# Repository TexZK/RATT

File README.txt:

RATT - Relatively Accurate TurnTable

For information about the project, please refer to:
./doc/reports/Report.pdf

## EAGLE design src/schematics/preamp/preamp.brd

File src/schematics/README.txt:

Source code for PCB schematics, developed with CadSoft EAGLE 6.2.0.

http://www.cadsoftusa.com/eagle/

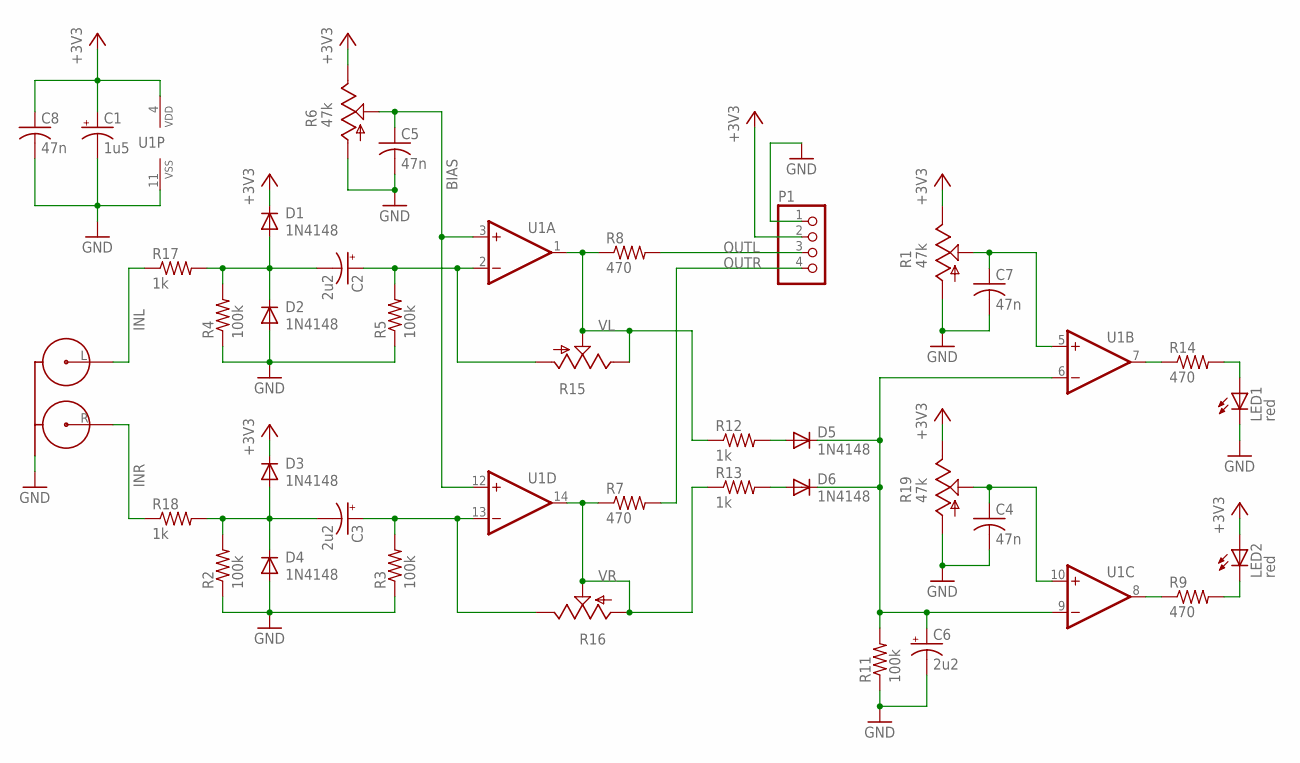
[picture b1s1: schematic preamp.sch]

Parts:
C1: 1u5; E2-4
C2, C3: 2u2; E2,5-5
C4, C5, C7, C8: 47n; C050-025X075
C6: 2u2; E2,5-6
D1, D2, D3, D4, D5, D6: 1N4148; DO35-5
LED1, LED2: red; LED3MM
P1: PINHD-1X4; 1X04
R1, R6, R19: 47k; PT-10S
R2, R3, R4, R5, R11: 100k; 0204/5
R7, R8, R9, R14: 470; 0204/5
R12, R13, R17, R18: 1k; 0204/5
R15, R16: TRIM_US-S63S; S63S
RCA1: RCA-2V
U1: MCP6024-I/P; DIL14

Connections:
+3V3: C1.+, C8.1, D1.C, D3.C, LED2.A, P1.2, R1.E, R6.E, R19.E, U1.4 (VDD)
BIAS: C5.1, R6.S, U1.3 (+IN), U1.12 (+IN)
GND: C1.-, C4.2, C5.2, C6.-, C7.2, C8.2, D2.A, D4.A, LED1.K (C), P1.1, R1.A, R2.1, R3.1, R4.1, R5.1, R6.A, R11.1, R19.A, RCA1.SHIELD, U1.11 (VSS)
INL: R17.1, RCA1.L
INR: R18.1, RCA1.R
unnamed: C4.1, R19.S, U1.10 (+IN)
unnamed: R9.1, U1.8 (OUT)
unnamed: C3.-, D3.A, D4.C, R2.2, R18.2
unnamed: C6.+, D5.C, D6.C, R11.2, U1.6 (-IN), U1.9 (-IN)
unnamed: C2.+, R5.2, R15.A, U1.2 (-IN)
unnamed: C7.1, R1.S, U1.5 (+IN)
unnamed: LED1.A, R14.2
unnamed: C2.-, D1.A, D2.C, R4.2, R17.2
unnamed: C3.+, R3.2, R16.E, U1.13 (-IN)
unnamed: D5.A, R12.2
unnamed: D6.A, R13.2
unnamed: LED2.K (C), R9.2
unnamed: R14.1, U1.7 (OUT)
OUTL: P1.3, R8.2
OUTR: P1.4, R7.2
VL: R8.1, R12.1, R15.E, R15.S, U1.1 (OUT)
VR: R7.1, R13.1, R16.A, R16.S, U1.14 (OUT)

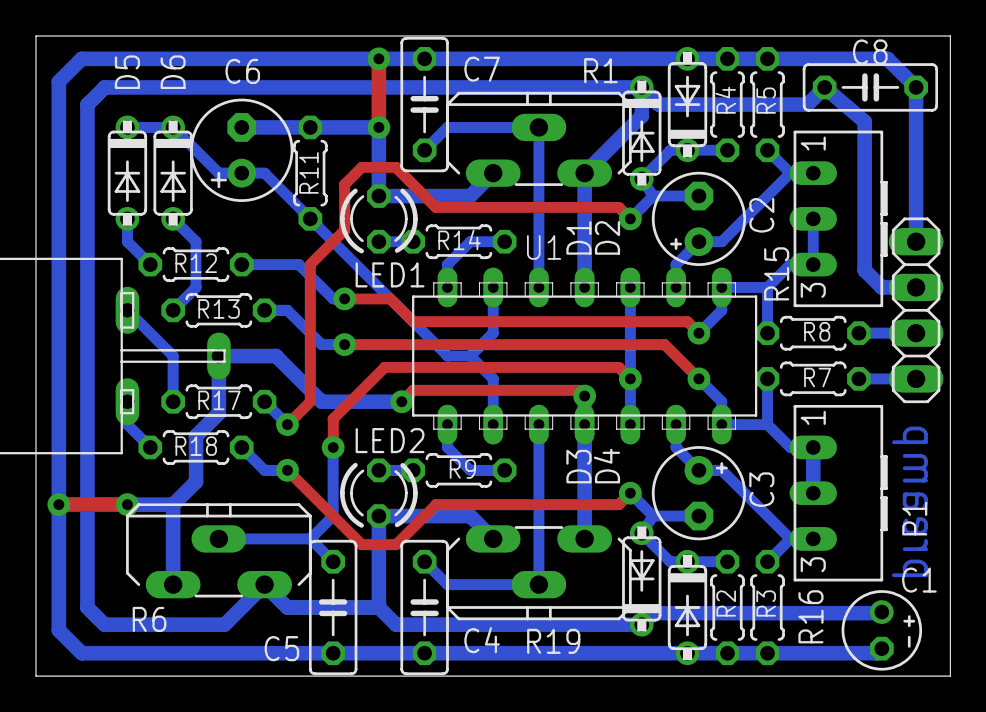
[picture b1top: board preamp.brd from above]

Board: 2 copper layers, 50.8 x 35.6 mm, 37 parts (0 on the bottom side), 22 nets.

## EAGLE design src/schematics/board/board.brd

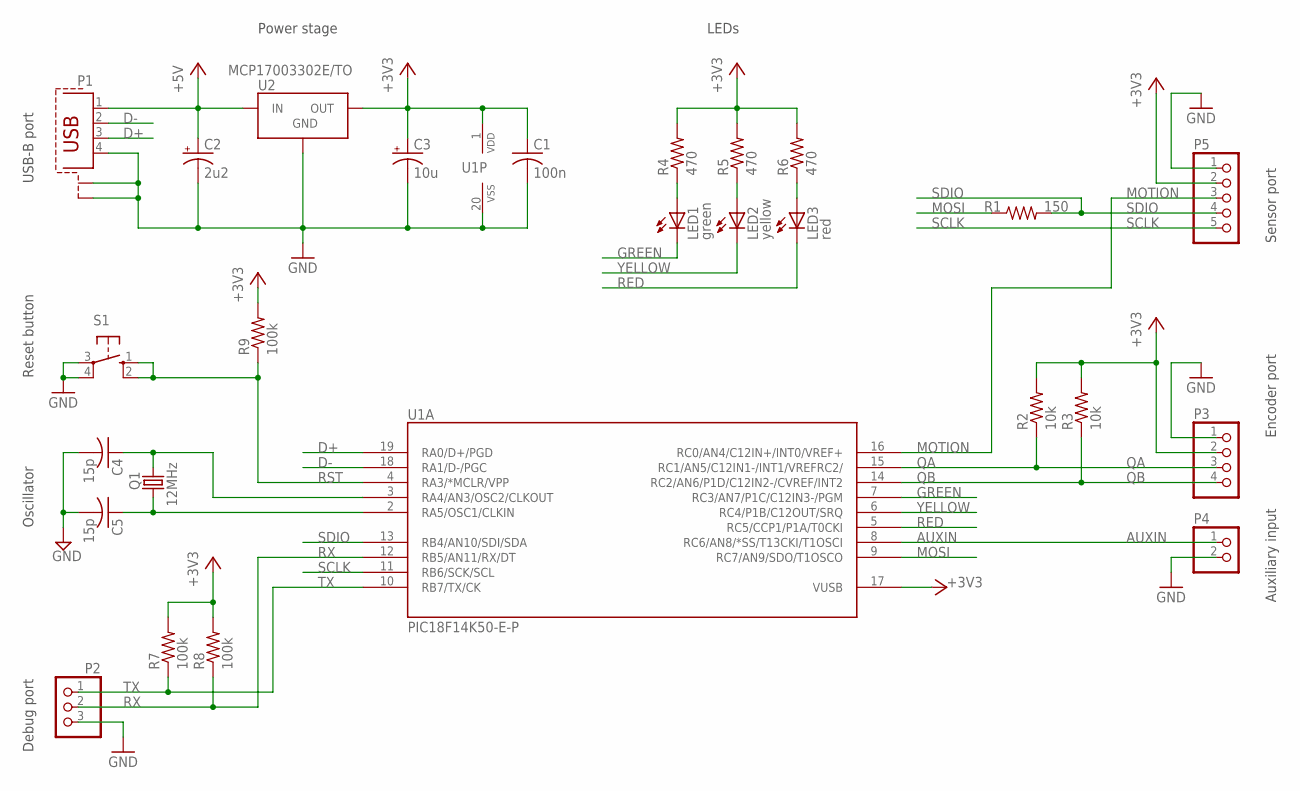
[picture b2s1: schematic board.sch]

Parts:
C1: 100n; C025-025X050
C2: 2u2; E2-5
C3: 10u; E2-5
C4, C5: 15p; C025-025X050
LED1: green; LED3MM
LED2: yellow; LED3MM
LED3: red; LED3MM
P1: PN61729-S
P2: PINHD-1X3; 1X03
P3: PINHD-1X4; 1X04
P4: PINHD-1X2; 1X02
P5: PINHD-1X5; 1X05
Q1: 12MHz; HC49/S
R1: 150; 0207/10
R2, R3: 10k; 0204/5
R4, R5, R6: 470; 0204/5
R7, R8, R9: 100k; 0204/5
S1: 10-XX; B3F-10XX
U1: PIC18F14K50-E-P; DIL20
U2: MCP17003302E/TO; TO-92

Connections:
+3V3: C1.1, C3.+, P3.2, P5.2, R2.2, R3.2, R4.2, R5.2, R6.2, R7.2, R8.2, R9.2, U1.1 (VDD), U1.17 (VUSB), U2.OUT
+5V: C2.+, P1.1, U2.IN
AUXIN: P4.1, U1.8 (RC6/AN8/*SS/T13CKI/T1OSCI)
D+: P1.3, U1.19 (RA0/D+/PGD)
D-: P1.2, U1.18 (RA1/D-/PGC)
GND: C1.2, C2.-, C3.-, C4.2, C5.2, P1.4, P1.S1, P1.S2, P2.3, P3.1, P4.2, P5.1, S1.3, S1.4 (P1), U1.20 (VSS), U2.GND
GREEN: LED1.K (C), U1.7 (RC3/AN7/P1C/C12IN3-/PGM)
MOSI: R1.1, U1.9 (RC7/AN9/SDO/T1OSCO)
MOTION: P5.3, U1.16 (RC0/AN4/C12IN+/INT0/VREF+)
unnamed: LED3.A, R6.1
unnamed: C4.1, Q1.1, U1.3 (RA4/AN3/OSC2/CLKOUT)
unnamed: C5.1, Q1.2, U1.2 (RA5/OSC1/CLKIN)
unnamed: LED2.A, R5.1
unnamed: LED1.A, R4.1
QA: P3.3, R2.1, U1.15 (RC1/AN5/C12IN1-/INT1/VREFRC2/)
QB: P3.4, R3.1, U1.14 (RC2/AN6/P1D/C12IN2-/CVREF/INT2)
RED: LED3.K (C), U1.5 (RC5/CCP1/P1A/T0CKI)
RST: R9.1, S1.1 (S), S1.2 (S1), U1.4 (RA3/*MCLR/VPP)
RX: P2.2, R8.1, U1.12 (RB5/AN11/RX/DT)
SCLK: P5.5, U1.11 (RB6/SCK/SCL)
SDIO: P5.4, R1.2, U1.13 (RB4/AN10/SDI/SDA)
TX: P2.1, R7.1, U1.10 (RB7/TX/CK)
YELLOW: LED2.K (C), U1.6 (RC4/P1B/C12OUT/SRQ)

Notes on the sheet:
Reset button
Oscillator
Debug port
USB-B port
Encoder port
Auxiliary input
Sensor port
Power stage
LEDs

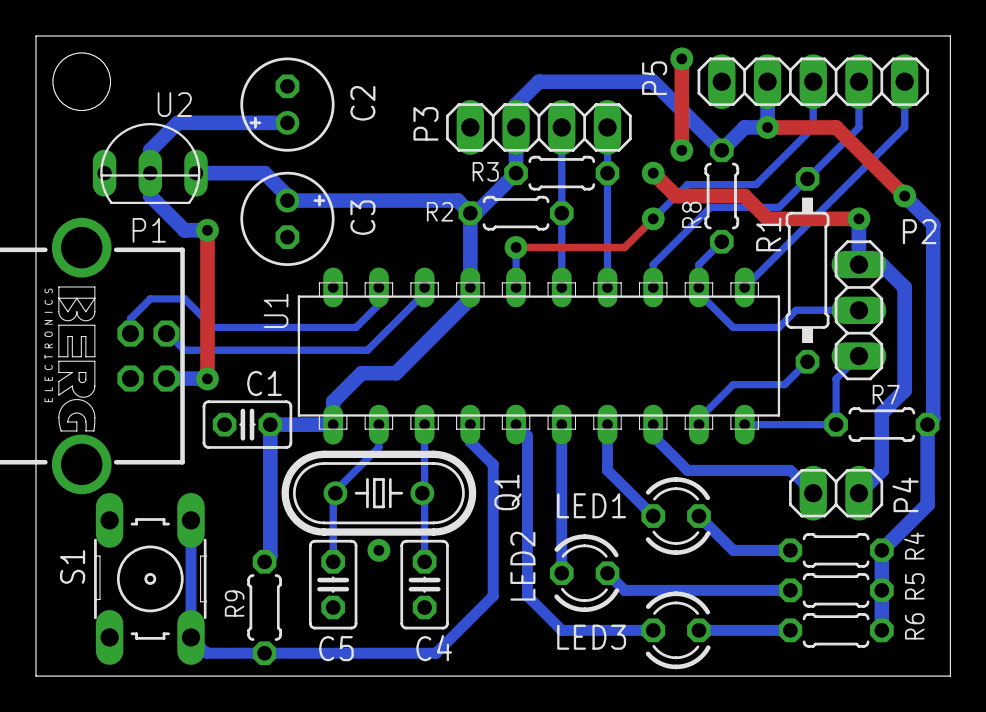
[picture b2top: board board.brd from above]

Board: 2 copper layers, 50.8 x 35.6 mm, 26 parts (0 on the bottom side), 23 nets.

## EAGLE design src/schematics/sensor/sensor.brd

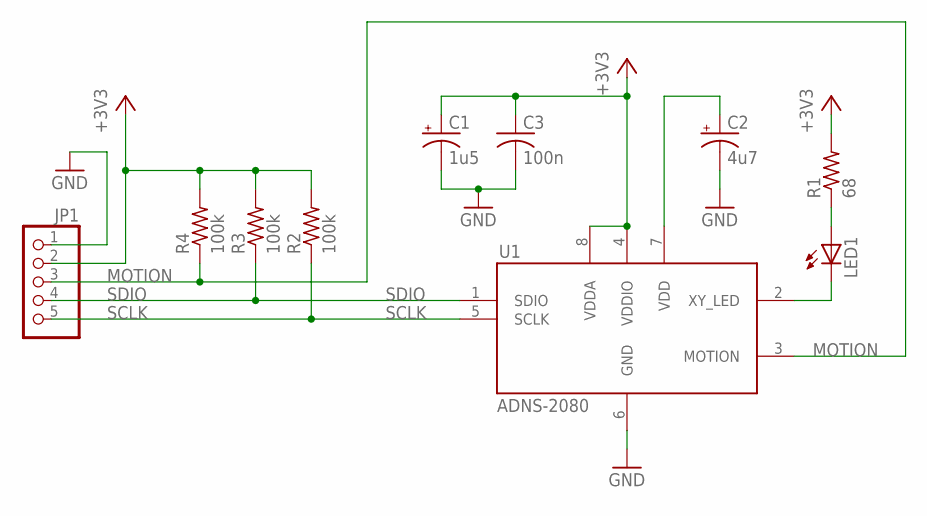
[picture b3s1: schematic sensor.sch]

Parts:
C1: 1u5; E2,5-5
C2: 4u7; E2,5-5
C3: 100n; C025-025X050
JP1: PINHD-1X5; 1X05
LED1: LED5MM
R1: 68; 0207/7
R2, R3, R4: 100k; 0204/5
U1: ADNS-2080; DIP8-OPTICAL

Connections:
+3V3: C1.+, C3.1, JP1.2, R1.2, R2.2, R3.2, R4.2, U1.4 (VDDIO), U1.8 (VDDA)
GND: C1.-, C2.-, C3.2, JP1.1, U1.6 (GND)
MOTION: JP1.3, R4.1, U1.3 (MOTION)
unnamed: C2.+, U1.7 (VDD)
unnamed: LED1.A, R1.1
unnamed: LED1.K (C), U1.2 (XY_LED)
SCLK: JP1.5, R2.1, U1.5 (SCLK)
SDIO: JP1.4, R3.1, U1.1 (SDIO)

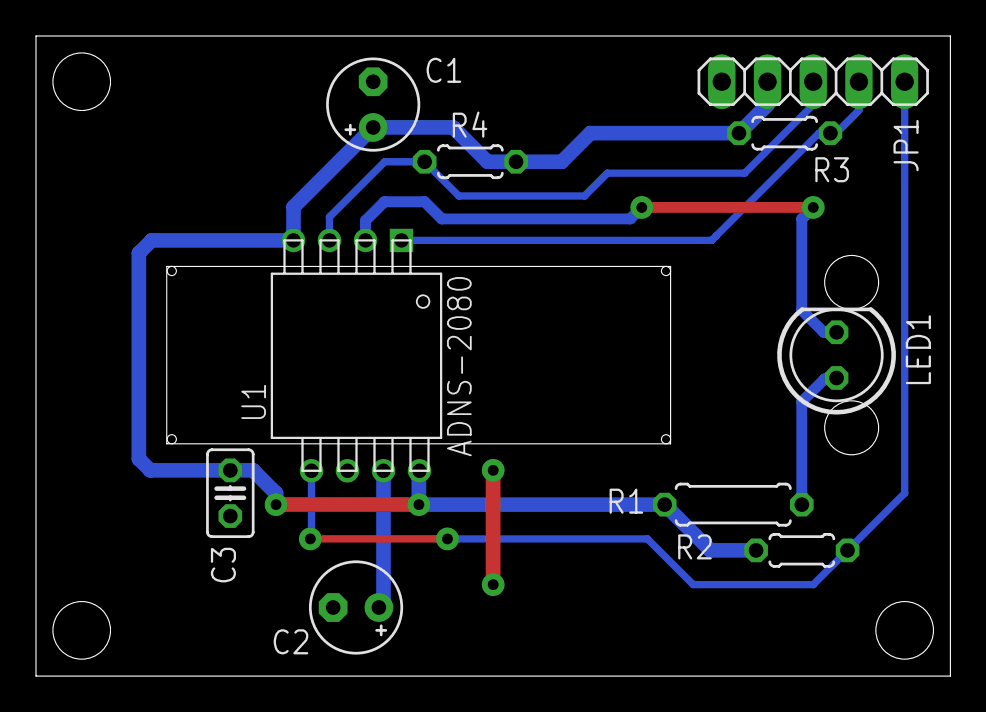
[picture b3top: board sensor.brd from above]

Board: 2 copper layers, 50.8 x 35.6 mm, 10 parts (0 on the bottom side), 8 nets.

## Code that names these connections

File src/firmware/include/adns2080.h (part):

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#define	ADNS_DLY_REST_DIS_MAX_S			      1				///< t_REST-DIS
#define	ADNS_DLY_PD_MAX_MS				     50				///< t_PD
#define	ADNS_DLY_WAKEUP_MAX_MS			     55				///< t_WAKEUP
#define	ADNS_DLY_R_SDIO_MAX_NS			    200				///< t_r-SDIO
#define	ADNS_DLY_F_SDIO_MAX_NS			    200				///< t_f-SDIO
#define	ADNS_DLY_DLY_SDIO_MAX_NS		    120				///< t_DLY-SDIO
#define	ADNS_DLY_HOLD_MIN_NS			    250				///< t_hold-SDIO
#define	ADNS_DLY_HOLD_MAX_NS			(1000000000 / ADNS_SPI_FREQ)	///< t_hold-SDIO
#define	ADNS_DLY_TIMEOUT_SDIO_MIN_MS	     50				///< t_timeout-SDIO
#define	ADNS_DLY_TSWR_MIN_MS			     20				///< t_SWR
#define	ADNS_DLY_TSWW_MIN_MS			     30				///< t_SWW
#define	ADNS_DLY_TSRX_MIN_NS			    250				///< t_SRW & t_SRR
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#define	ADNS_TRIS_MISO					TRISBbits.TRISB4	///< SPI MISO/SDI
#define	ADNS_TRIS_MOSI					TRISCbits.TRISC7	///< SPI MOSI/SDO
#define	ADNS_TRIS_SCLK					TRISBbits.TRISB6	///< SPI SCLK/SCK
#define	ADNS_TRIS_MOTION				TRISCbits.TRISC0	///< MOTION IRQ

#define	ADNS_PIN_MISO					PORTBbits.RB4		///< SPI MISO/SDI
#define	ADNS_PIN_MOSI					PORTCbits.RC7		///< SPI MOSI/SDO
#define	ADNS_PIN_SCLK					PORTBbits.RB6		///< SPI SCLK/SCK
#define	ADNS_PIN_MOTION					PORTCbits.RC0		///< MOTION IRQ

#define	ADNS_LAT_MISO					LATBbits.LATB4		///< SPI MISO/SDI
#define	ADNS_LAT_MOSI					LATCbits.LATC7		///< SPI MOSI/SDO
#define	ADNS_LAT_SCLK					LATBbits.LATB6		///< SPI SCLK/SCK
#define	ADNS_LAT_MOTION					LATCbits.LATC0		///< MOTION IRQ


// Interrupt settings
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// Register addresses (see datasheet for description)
#define	ADNS_REG_PROD_ID				0x00				///< Product ID
#define	ADNS_REG_REV_ID					0x01				///< Revision ID
#define	ADNS_REG_MOTION_ST				0x02				///< Motion Status 
#define	ADNS_REG_DELTA_X				0x03				///< Lower byte of Delta_X 
#define	ADNS_REG_DELTA_Y				0x04				///< Lower byte of Delta_Y
#define	ADNS_REG_SQUAL					0x05				///< Squal Quality
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#define	ADNS_REG_RESET					0x3A				///< Reset
#define	ADNS_REG_NOT_REV_ID				0x3F				///< Inverted Revision ID
#define	ADNS_REG_LED_CTRL				0x40				///< LED Control
#define	ADNS_REG_MOTION_CTRL			0x41				///< Motion Control
#define	ADNS_REG_BURST_READ_FIRST		0x42				///< Burst Read Starting Register 
#define	ADNS_REG_BURST_READ_LAST		0x44				///< Burst Read Ending Register
#define	ADNS_REG_REST_MODE_CONFIG		0x45				///< Rest Mode Coni  guration
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
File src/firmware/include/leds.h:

/**
 * LEDs driver.
 *
 * This file contains the definitions to handle the LEDs.
 *
 * @author Andrea "TexZK" Zoppi
 *
 */

#ifndef __LEDS_H__
#define	__LEDS_H__


//\\//\\//\\//\\//\\//\\//\\//\\//\\//\\//\\//\\//\\//\\//\\//\\//\\//\\//\\//
// HEADERS


//\\//\\//\\//\\//\\//\\//\\//\\//\\//\\//\\//\\//\\//\\//\\//\\//\\//\\//\\//
// GLOBAL DEFINITIONS

// Pins configuration
#define	LEDS_PORT				PORTC				///< LEDs port
#define	LEDS_TRIS				TRISC				///< LEDs port tristate
#define	LEDS_MASK				0b00111000			///< LEDs port/tristate mask

#define	LEDS_TRIS_GREEN			TRISCbits.TRISC3	///< Green LED pin tristate
#define	LEDS_TRIS_YELLOW		TRISCbits.TRISC4	///< Yellow LED pin tristate
#define	LEDS_TRIS_RED			TRISCbits.TRISC5	///< Red LED pin tristate

#define	LEDS_PIN_GREEN			PORTCbits.RC3		///< Green LED pin
#define	LEDS_PIN_YELLOW			PORTCbits.RC4		///< Yellow LED pin
#define	LEDS_PIN_RED			PORTCbits.RC5		///< Red LED pin

#define	LEDS_LAT_GREEN			LATCbits.LATC3		///< Green LED latch
#define	LEDS_LAT_YELLOW			LATCbits.LATC4		///< Yellow LED latch
#define	LEDS_LAT_RED			LATCbits.LATC5		///< Red LED latch


// Shorthands
#define	GREEN_LED				LEDS_LAT_GREEN		///< Shortcut for green LED bit
#define	YELLOW_LED				LEDS_LAT_YELLOW		///< Shortcut for yellow LED bit
#define	RED_LED					LEDS_LAT_RED		///< Shortcut for red LED bit

#define	LED_ON					0					///< Incoming current, LED lit
#define	LED_OFF					1					///< Pull-up, LED off


//\\//\\//\\//\\//\\//\\//\\//\\//\\//\\//\\//\\//\\//\\//\\//\\//\\//\\//\\//
// GLOBAL VARIABLES


//\\//\\//\\//\\//\\//\\//\\//\\//\\//\\//\\//\\//\\//\\//\\//\\//\\//\\//\\//
// GLOBAL PROTOTYPES

/**
 * Initializes the LEDs module.
 */
void Leds_Initialize( void );


/**
 * Turns LEDs as if they were bits:
 * 	GREEN	= bit 0,
 *	YELLOW	= bit 1,
 *	RED		= bit 2
 *
 * @param value
 *		3-bits value [RYG].
 */
#define	Leds_BinaryValue( value )	{	\
	GREEN_LED = !((value) & 0b001);		\
	YELLOW_LED = !((value) & 0b010);	\
	RED_LED = !((value) & 0b100);		\
}


#endif	/* !__LEDS_H__ */

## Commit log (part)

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2012-03-08 Datasheets and report source code
    Added datasheets for Avago ADNS-2080 and Microchip PIC18LF14K50, and the
    source code for the LaTeX report.
    Andrea Zoppi
2012-03-10 Sensor PCB updates
    Minor changes to the sensor module PCB layout.
    Andrea Zoppi
2012-03-10 PCBs updated
    Minor changes were done to both the main board and sensor module PCB
    layouts.
    Andrea Zoppi
2012-03-10 Code refactoring
    Main functions are now inside the "app" module.
    User USB functions were moved to the "usb_user" module.
    Andrea Zoppi
2012-03-11 Small fixes to firmware
    A bootloader definitions file was modularized, and a few initialization
    routines were rearranged (just some refactoring).
    Andrea Zoppi
2012-03-11 Added UART pull-ups
    Added pull-ups to the UART port, so that there are never mistaken signals.
    They are not critical, but may help in keeping consistent values,
    especially for the receiver.
    Andrea Zoppi
2012-03-12 Hand-written UART functions
    UART functions are now hand-written, because library functions provided by
    Microchip don't always work properly.
    Andrea Zoppi
2012-03-12 Hand-written SPI code
    SPI functions were ported by hand, so that the code behaves exactly as
    expected.
    Andrea Zoppi
2012-03-12 Improved debug info of ADNS module
    The yellow LED is used to see if there is some buffered motion, ready to
    be sent over USB.
    Macros with integrated pointer casting were added, so that literal strings
    can be written without manual casting each time.
    Andrea Zoppi
2012-03-12 Debug console now working properly
    It is possible to send characters properly over the UART console.
    Andrea Zoppi
2012-03-13 Added user button pull-up
    A pull-up resistor was added to the user button, because the built-in weak
    pull-up of the MCU does not work properly at power-up.
    Andrea Zoppi
2012-03-13 Improved debug messaging system
    The debug console is now interrupt-driven.
    Some common strings can be called through dedicated Debug_PrintConst_*
    calls, so that ROM memory occupation is minimized.
    USB state changes are now notified through [!USB_<state>] event messages.
    Andrea Zoppi
2012-03-13 ADNS register configuration and improvements
    Added register initialization for ADNS chip.
    Performance improved when reading/writing to it, by removing useless code.
    Andrea Zoppi
2012-03-13 Untracking MPLAB workspaces
    MPLAB workspaces always differ between machines and are autosaved, which
    makes their tracking annoying.
    Andrea Zoppi
2012-03-14 Added export to Eagle working dir and fixed import
    Andrea Zoppi
2012-03-15 ADNS operation only if communication test passes
    Andrea Zoppi
2012-03-15 Fixed missing R/W bit in address writing
    The MSb indicating a Write/Read operation on that register was missing,
    and has been added to ADNS register write/read function calls.
    Andrea Zoppi
2012-03-15 MOSI held in HiZ after reading
    The MOSI pin must be kept in HiZ state after finishing a write, because
    the SDIO line is still driven by ADNS-2080 until the next falling edge of
    SCLK.
    Andrea Zoppi
2012-03-15 Improved debug messages
    Hex byte nibbles are printed in the right order (high nibble, low nibble).
    Events now use '@' instead of '!' to avoid misleading interpretation as
    NOT operator ("[@EVENT]" instead of "[!EVENT]").
    Misc fixes.
    Andrea Zoppi
2012-03-15 Automatic console flush and cleaner button timing
    The debug console is automatically flushed at each background task cycle.
    The user button is debounced with a cleader code.
    Andrea Zoppi
2012-03-15 Fixed Motion Burst operations
    The Motion burst did not leave the SDIO line driven by ADNS after reading
    values; it is fixed now.
    Also, the values been read were completely messed up. It is now possible
    to read 12-bits values and convert them into 16-bits signed integers.
    Other small changes, just for readability.
    Andrea Zoppi
2012-03-16 Analog incremental encoder pins and aux input
    The incremental encoder pins and the auxiliary input are now initialized
    as analog inputs.
    Andrea Zoppi
2012-03-16 Comparator interrupts defined
    Interrupts for comparators were defined and integrated with the main
    application of the firmware.
    Andrea Zoppi
2012-03-16 Incremental encoder and MOTION pins updated
    Pins for incremental encoder signals (ENC_A and ENC_B), and the MOTION
    signal have ben re-routed to the correct PIC pins, according to the
    changes made in the latest commits.
    Andrea Zoppi
2012-03-16 Encoder interrupts implemented
    Incremental encoder interrupts were implemented. They increment/decrement
    the delta accumulator. After reading it, it is cleared.
    Andrea Zoppi
2012-03-18 Added preamp module for squaring waves
    A pre-amplificator module was added, so that one can use the timecode
    signal from some DVS CDs or vinyls.
    They are always encoded as amplitude-modulated sine/cos waves, so that it
    is always possible to square the waves and obtain a 2-bits incremental
    encoder signal, provided that the volume is reasonable.
    A red LED will signal to the user that the signal amplitude is not enough
2012-03-18 Added pre-compiled delays routines
    An object file containing pre-compiled delay routines was added.
    These routines are compiled without any advanced optimization, so that
    blocking delays are coded properly, without removing the "useless" code.
    Andrea Zoppi
2012-03-19 Improved debug console and interrupts
    The debug console should now work with nested interrupts.
    Global interrupts are now controllable with global macros defined in
    "app.h".
    The debug console function synthesis can be switched on or off, through
    configuration definitions.
    Inside the debug code, the user can choose to compile strings, integral
2012-03-19 Minor debug additions
    Just some small refactoring and definitions.
    Andrea Zoppi
2012-03-19 Improved interrupt handling
    Added a better locking system, which locks only "tasks" with priority
    higher than the lock caller. In this way, things such nested console
    prints should not give incorrect output strings.
    Incremental encoder interrupts are temporarily disabled (WIP), because
    they currently block the execution someway.
    Andrea Zoppi
2012-03-20 Better tracking of encoder state
    The incremental encoder state now tracks direction and its records have
    been refactored in order to support the right data type.
    Andrea Zoppi
2012-03-20 Fixed invalid encoder states
    Invalid encoder states won't do anything.
    Andrea Zoppi
2012-03-20 Added locking timestamp reading
    Reading the application timestamp is now done with a locking function.
    Andrea Zoppi
2012-03-21 Added double RCA connector to preamp module
    Andrea Zoppi
2012-03-22 Window comparator for preamp calibration
    The positive voltage reference for opamps is now reduced to a simple
    potentiometer, sithout impedance decoupling (not strictly needed).
    Two opamps are used as comparators for windowing of the rectified input
    signals. This way it is possible to warn the user if the signal is too low
    like before (bad comparator results) and also if the signal is too strong,
    thus leading to a potentially wring duty cycle of the squared wave.
2012-03-27 USB descriptor and small changes
    The USB descriptor has the temporary VID/PID = 0xDEAD/0xBEEF.
    Strings have been changed, too.
    Small fixes for LED and debugging.
    Andrea Zoppi
2012-05-17 Latex report sketch
    The latex report template was cleaned up.
    A sketch of the report structure was written.
    Andrea Zoppi
2012-05-18 Timecode description
    Added first part of the timecode emulation description inside the report.
    Andrea Zoppi
2012-05-19 Simplified approach brief descriptions
    Andrea Zoppi
2012-05-21 Added some sensor documentation
    Andrea Zoppi
2012-06-01 Added serato timecode image and some text
    Andrea Zoppi
2012-06-08 Started advanced approach documentation
    Andrea Zoppi
2012-07-30 Device library behavior and interrupt changes
    The device API was changed so that the incremental encoder and the mouse
    sensor status are cached into global variables, instead of passing values
    by function calls, since there are not multiple instances of such devices.
    This improves performance and optimizes memory usage.
    It is now possible to choose if the mouse sensor code reacts to interrupts
    or polls the status. Since the interrupt is simply cached and just wastes
2012-07-30 Motion interrupt enabled again
    The motion interrupt was enabled again, until a stable polling method is
    developed. Currently, polling the MOTION pin always returns a low value,
    while it should give it only when there is actually new data.
    Andrea Zoppi
2012-07-31 Fixed HID report size
    The HID report size is now equal to the actual meaningful data contained.
    Andrea Zoppi
2012-08-01 Some encoder tweaks
    The mouse sensor is now forced to 2000 DPI.
    The incremental encoder now correctly reads a quadrature signal derived
    from a common DVS timecode.
    Andrea Zoppi
2012-08-04 Motion accumulator inverted
    The mouse motion deltas are now subtracted to the accumulator. This lets
    the user to put the RATT device on the top of a turntable.
    Andrea Zoppi
2012-08-06 Bibliography fixes and more figures
    The biblography format is now more pleasant.
    Some figures were added to the report.
    Small fixes.
    Andrea Zoppi
2012-08-06 Added some timing diagrams
    Some timing diagrams were added to the documentation.
    Other small fixes and additions.
    Andrea Zoppi
2012-08-07 Documentation structure reworked
    The appendices of the documentation were moved after the current market
    survey.
    The I2C bus descritption was removed, because actually no mouse sensors
    use it.
    Small fixes.
    Andrea Zoppi
2012-08-08 Added Virtual DJ mapping documentation
    The Virtual DJ device description and its mapping were added to the
    documentation.
    Other small fixed.
    Andrea Zoppi
2012-08-10 Small fixes
    Small fixes in the definition and use of the HID report.
    Andrea Zoppi
2012-08-10 Added HID description
    Added HID protocol description to the documentation.
    Small fixes.
    Andrea Zoppi
2012-08-12 Added computations spreadsheet
    A spreadsheet for computations was added. It also simplifies the update of
    the report source code, with computation data.
    Andrea Zoppi
2012-08-12 Added MOTION delay screenshots
    Oscilloscope screenshots for MOTION interrupt delays for slow and fast
    motions were added.
    Andrea Zoppi
2012-08-12 Report sources moved
    The documentation (report) sources were moved into the /src directory.
    Andrea Zoppi
2012-08-13 Added XML files for Virtual DJ
    Device and mapping XML files for Virtual DJ were added. Also, some scripts
    automate the installation of such files on both Windows and MacOSX (Unix).
    Small changes.
    Andrea Zoppi
2012-08-14 Added firmware framework and ADNS-3550 pictures
    A logical view of the firmware framework was added to the simplified
    approach documentation.
    An alternative sensor, the Avago ADNS-3550, was proposed in the advanced
    approach.
    Andrea Zoppi
2012-08-18 Started advanced firmawre description
    A first sketch of the dvanced approach firmware description was written.
    A logical diagram of it was added.
    Small fixes
    Andrea Zoppi
2012-08-19 Advanced firmware description updated
    The description of the advanced approach firmware was updated, and is now
    almost completed.
    Andrea Zoppi
2012-09-01 Computations updated
    Computations for the measurement perimeter dots were updated.
    Andrea Zoppi
2012-09-02 Removed XML comments
    Comments inside the XML files for VirtualDJ were removed, because that
    software does not accept them otherwise...
    Andrea Zoppi
2012-09-04 Added Tascam and github references
    References to the Tascam TT-M1 and the RATT repository were added to the
    technical report.
    Andrea Zoppi
2012-09-04 Added README.txt to important directories
    Andrea Zoppi
